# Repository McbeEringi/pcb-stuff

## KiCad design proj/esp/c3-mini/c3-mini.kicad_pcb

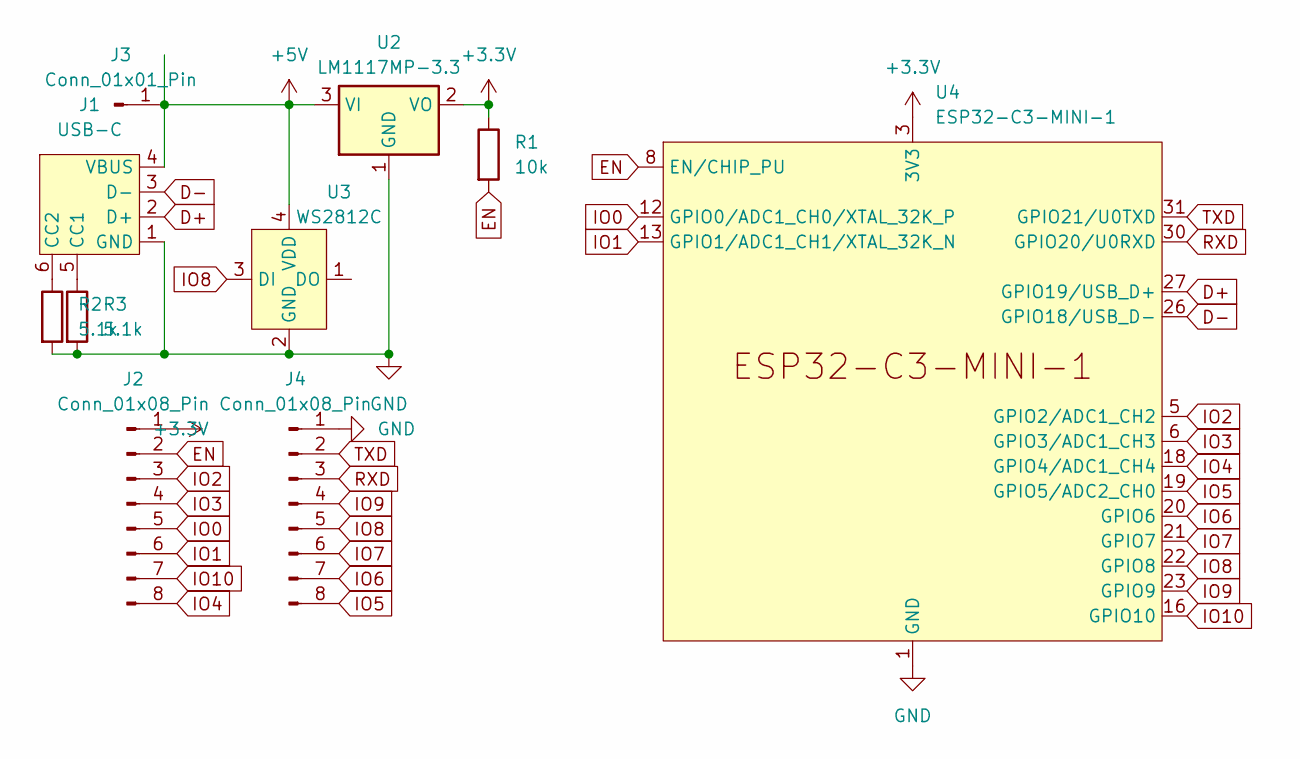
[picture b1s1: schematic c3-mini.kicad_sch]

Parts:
J1: USB-C
J2, J4: Conn_01x08_Pin; PinHeader_1x08_P2.54mm_Vertical
J3: Conn_01x01_Pin; PinHeader_1x01_P2.54mm_Vertical
R1: 10k; R_0603_1608Metric
R2, R3: 5.1k; R_0603_1608Metric
U2: LM1117MP-3.3; SOT-223-3_TabPin2
U3: WS2812C; WS2812C-2020
U4: ESP32-C3-MINI-1

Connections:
+3.3V: J2.1, R1.1, U2.2 (VO), U4.3 (3V3)
+5V: J1.4 (VBUS), J3.1, U2.3 (VI), U3.4 (VDD)
D+: J1.2 (D+), U4.27 (GPIO19/USB_D+)
D-: J1.3 (D-), U4.26 (GPIO18/USB_D-)
EN: J2.2, R1.2, U4.8 (EN/CHIP_PU)
GND: J1.1 (GND), J4.1, R2.2, R3.2, U2.1 (GND), U3.2 (GND), U4.1 (GND), U4.2 (GND), U4.11 (GND), U4.14 (GND), U4.36 (GND), U4.37 (GND), U4.38 (GND), U4.39 (GND), U4.40 (GND), U4.41 (GND), U4.42 (GND), U4.43 (GND), U4.44 (GND), U4.45 (GND), U4.46 (GND), U4.47 (GND), U4.48 (GND), U4.49 (GND), U4.50 (GND), U4.51 (GND), U4.52 (GND), U4.53 (GND)
IO0: J2.5, U4.12 (GPIO0/ADC1_CH0/XTAL_32K_P)
IO1: J2.6, U4.13 (GPIO1/ADC1_CH1/XTAL_32K_N)
IO2: J2.3, U4.5 (GPIO2/ADC1_CH2)
IO3: J2.4, U4.6 (GPIO3/ADC1_CH3)
IO4: J2.8, U4.18 (GPIO4/ADC1_CH4)
IO5: J4.8, U4.19 (GPIO5/ADC2_CH0)
IO6: J4.7, U4.20 (GPIO6)
IO7: J4.6, U4.21 (GPIO7)
IO8: J4.5, U3.3 (DI), U4.22 (GPIO8)
IO9: J4.4, U4.23 (GPIO9)
IO10: J2.7, U4.16 (GPIO10)
unnamed: J1.5 (CC1), R3.1
unnamed: J1.6 (CC2), R2.1
RXD: J4.3, U4.30 (GPIO20/U0RXD)
TXD: J4.2, U4.31 (GPIO21/U0TXD)

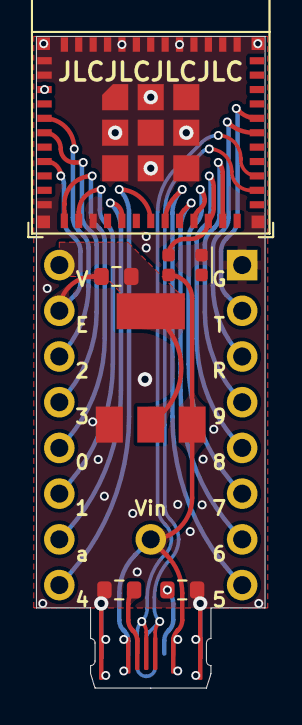
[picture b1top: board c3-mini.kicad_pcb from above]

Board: 2 copper layers, 12.7 x 36.2 mm, 10 parts (0 on the bottom side), 21 nets.

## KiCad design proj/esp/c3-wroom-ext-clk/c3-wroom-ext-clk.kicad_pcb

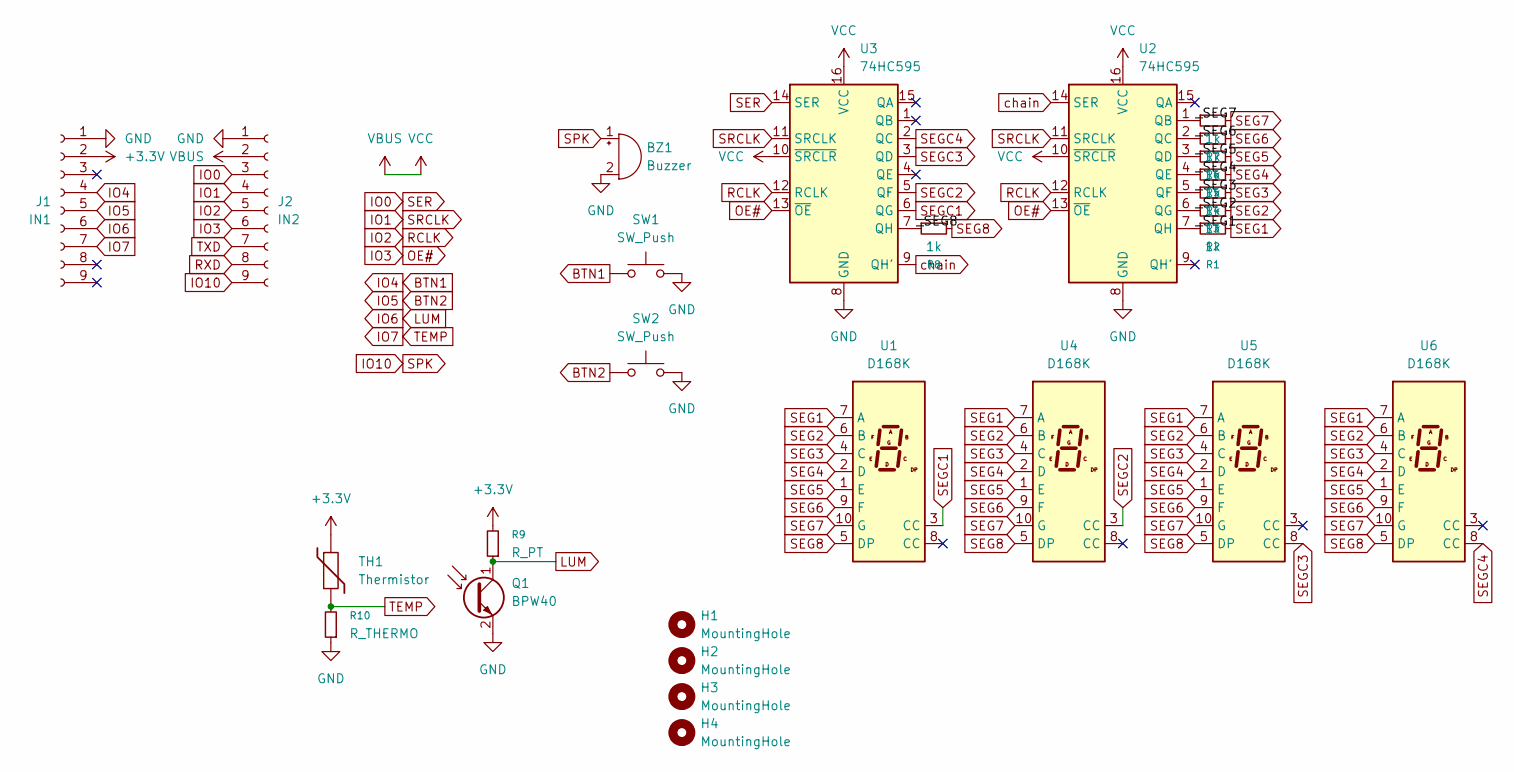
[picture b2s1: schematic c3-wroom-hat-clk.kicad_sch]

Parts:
BZ1: Buzzer; Buzzer_TDK_PS1240P02BT_D12.2mm_H6.5mm
H1, H2, H3, H4: MountingHole; MountingHole_3.2mm_M3
J1: IN1; PinSocket_1x09_P2.54mm_Vertical
J2: IN2; PinSocket_1x09_P2.54mm_Vertical
Q1: BPW40; LED_D5.0mm_Clear
R1, R2, R3, R4, R5, R6, R7, R8: 1k; R_0603_1608Metric
R9: R_PT; R_0603_1608Metric
R10: R_THERMO; R_0603_1608Metric
SW1, SW2: SW_Push; alps-skrg
TH1: Thermistor; R_0603_1608Metric
U1, U4, U5, U6: D168K; D1X8K
U2, U3: 74HC595; TSSOP-16_4.4x5mm_P0.65mm

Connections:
+3.3V: J1.2, R9.2, TH1.1
/_SEG1: R1.1, U2.7 (QH)
/_SEG2: R2.1, U2.6 (QG)
/_SEG3: R3.1, U2.5 (QF)
/_SEG4: R4.1, U2.4 (QE)
/_SEG5: R5.1, U2.3 (QD)
/_SEG6: R6.1, U2.2 (QC)
/_SEG7: R7.1, U2.1 (QB)
/_SEG8: R8.1, U3.7 (QH)
BTN1: J1.4, SW1.1
BTN2: J1.5, SW2.1
GND: BZ1.2 (-), J1.1, J2.1, Q1.2 (E), R10.1, SW1.2, SW2.2, U2.8 (GND), U3.8 (GND)
IO0: J2.3, U3.14 (SER)
IO1: J2.4, U2.11 (SRCLK), U3.11 (SRCLK)
IO2: J2.5, U2.12 (RCLK), U3.12 (RCLK)
IO3: J2.6, U2.13 (~OE), U3.13 (~OE)
IO6: J1.6, Q1.1 (C), R9.1
IO7: J1.7, R10.2, TH1.2
IO10: BZ1.1 (+), J2.9
RXD: J2.8
SEG1: R1.2, U1.7 (A), U4.7 (A), U5.7 (A), U6.7 (A)
SEG2: R2.2, U1.6 (B), U4.6 (B), U5.6 (B), U6.6 (B)
SEG3: R3.2, U1.4 (C), U4.4 (C), U5.4 (C), U6.4 (C)
SEG4: R4.2, U1.2 (D), U4.2 (D), U5.2 (D), U6.2 (D)
SEG5: R5.2, U1.1 (E), U4.1 (E), U5.1 (E), U6.1 (E)
SEG6: R6.2, U1.9 (F), U4.9 (F), U5.9 (F), U6.9 (F)
SEG7: R7.2, U1.10 (G), U4.10 (G), U5.10 (G), U6.10 (G)
SEG8: R8.2, U1.5 (DP), U4.5 (DP), U5.5 (DP), U6.5 (DP)
SEGC1: U1.3 (CC), U3.6 (QG)
SEGC2: U3.5 (QF), U4.3 (CC)
SEGC3: U3.3 (QD), U5.8 (CC)
SEGC4: U3.2 (QC), U6.8 (CC)
TXD: J2.7
VBUS: J2.2, U2.10 (~SRCLR), U2.16 (VCC), U3.10 (~SRCLR), U3.16 (VCC)
chain: U2.14 (SER), U3.9 (QH')

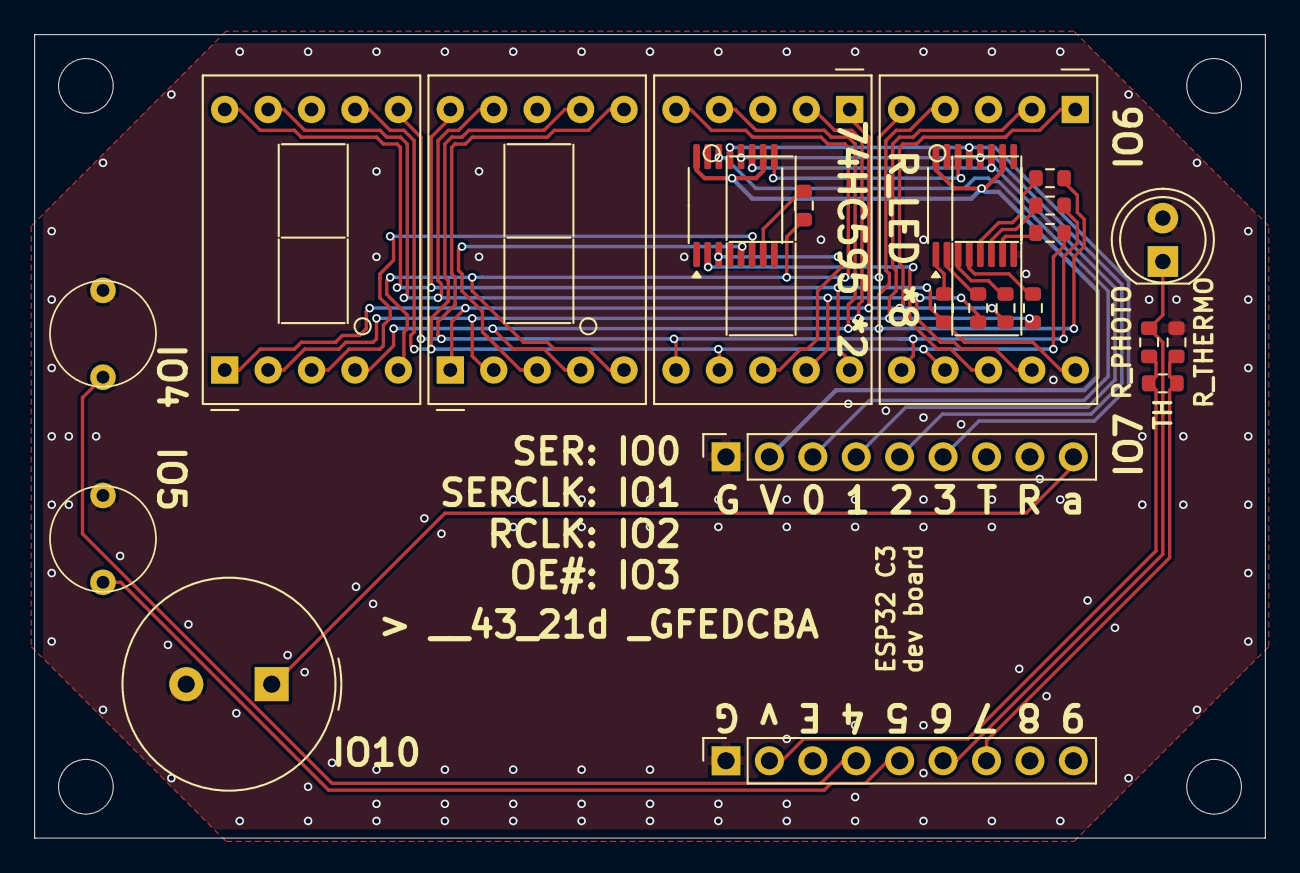
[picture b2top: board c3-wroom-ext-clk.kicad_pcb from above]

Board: 2 copper layers, 72.0 x 47.0 mm, 27 parts (0 on the bottom side), 33 nets.

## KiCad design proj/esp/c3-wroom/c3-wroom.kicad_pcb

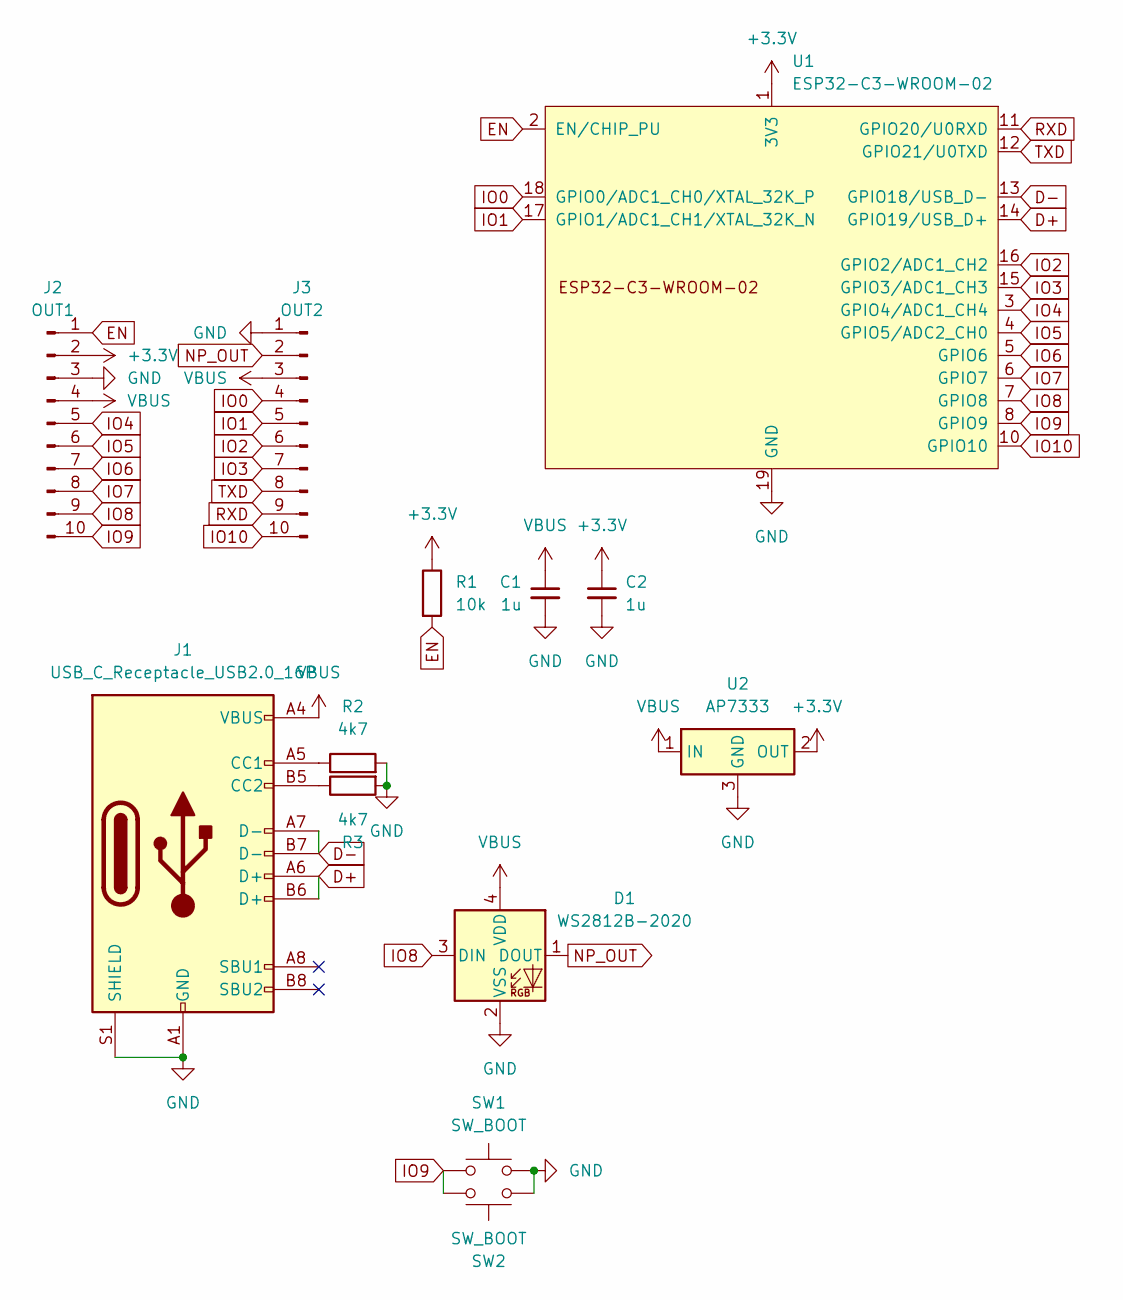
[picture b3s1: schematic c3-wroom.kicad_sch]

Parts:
C1, C2: 1u; C_0603_1608Metric
D1: WS2812B-2020; LED_WS2812B-2020_PLCC4_2.0x2.0mm
J1: USB_C_Receptacle_USB2.0_16P; USB_C_Receptacle_GCT_USB4105-xx-A_16P_TopMnt_Horizontal
J2: OUT1; PinHeader_1x10_P2.54mm_Vertical
J3: OUT2; PinHeader_1x10_P2.54mm_Vertical
R1: 10k; R_0603_1608Metric
R2, R3: 4k7; R_0603_1608Metric
SW1: SW_BOOT; alps-skrg
SW2: SW_BOOT; alps-skrp
U1: ESP32-C3-WROOM-02
U2: AP7333; SOT-23-3

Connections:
+3.3V: C2.1, J2.2, R1.1, U1.1 (3V3), U2.2 (OUT)
D+: J1.A6 (D+), J1.B6 (D+), U1.14 (GPIO19/USB_D+)
D-: J1.A7 (D-), J1.B7 (D-), U1.13 (GPIO18/USB_D-)
EN: J2.1, R1.2, U1.2 (EN/CHIP_PU)
GND: C1.2, C2.2, D1.2 (VSS), J1.A1 (GND), J1.A12 (GND), J1.B1 (GND), J1.B12 (GND), J1.S1 (SHIELD), J2.3, J3.1, R2.2, R3.2, SW1.2, SW2.2, U1.9 (GND), U1.19 (GND), U2.3 (GND)
IO0: J3.4, U1.18 (GPIO0/ADC1_CH0/XTAL_32K_P)
IO1: J3.5, U1.17 (GPIO1/ADC1_CH1/XTAL_32K_N)
IO2: J3.6, U1.16 (GPIO2/ADC1_CH2)
IO3: J3.7, U1.15 (GPIO3/ADC1_CH3)
IO4: J2.5, U1.3 (GPIO4/ADC1_CH4)
IO5: J2.6, U1.4 (GPIO5/ADC2_CH0)
IO6: J2.7, U1.5 (GPIO6)
IO7: J2.8, U1.6 (GPIO7)
IO8: D1.3 (DIN), J2.9, U1.7 (GPIO8)
IO9: J2.10, SW1.1, SW2.1, U1.8 (GPIO9)
IO10: J3.10, U1.10 (GPIO10)
NP_OUT: D1.1 (DOUT), J3.2
unnamed: J1.A5 (CC1), R2.1
unnamed: J1.B5 (CC2), R3.1
RXD: J3.9, U1.11 (GPIO20/U0RXD)
TXD: J3.8, U1.12 (GPIO21/U0TXD)
VBUS: C1.1, D1.4 (VDD), J1.A4 (VBUS), J1.A9 (VBUS), J1.B4 (VBUS), J1.B9 (VBUS), J2.4, J3.3, U2.1 (IN)

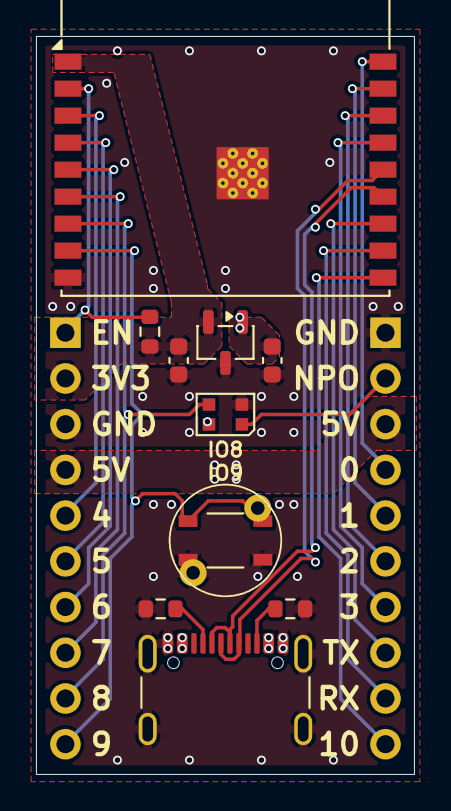
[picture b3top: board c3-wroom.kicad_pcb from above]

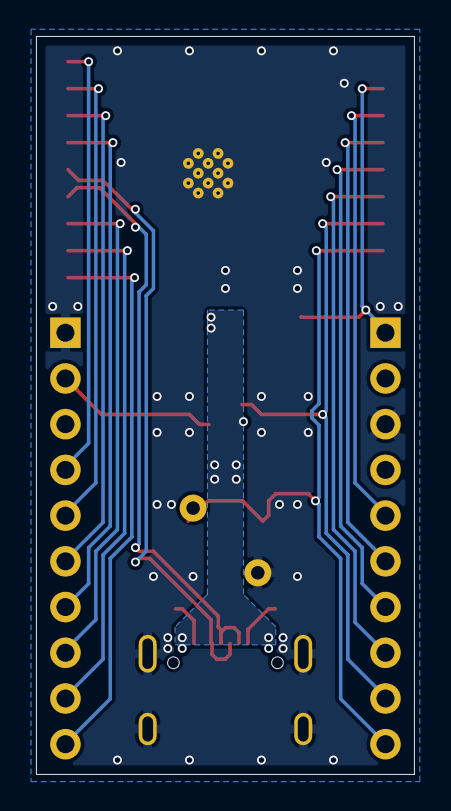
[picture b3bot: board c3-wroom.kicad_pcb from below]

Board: 2 copper layers, 21.0 x 41.0 mm, 13 parts (2 on the bottom side), 22 nets.

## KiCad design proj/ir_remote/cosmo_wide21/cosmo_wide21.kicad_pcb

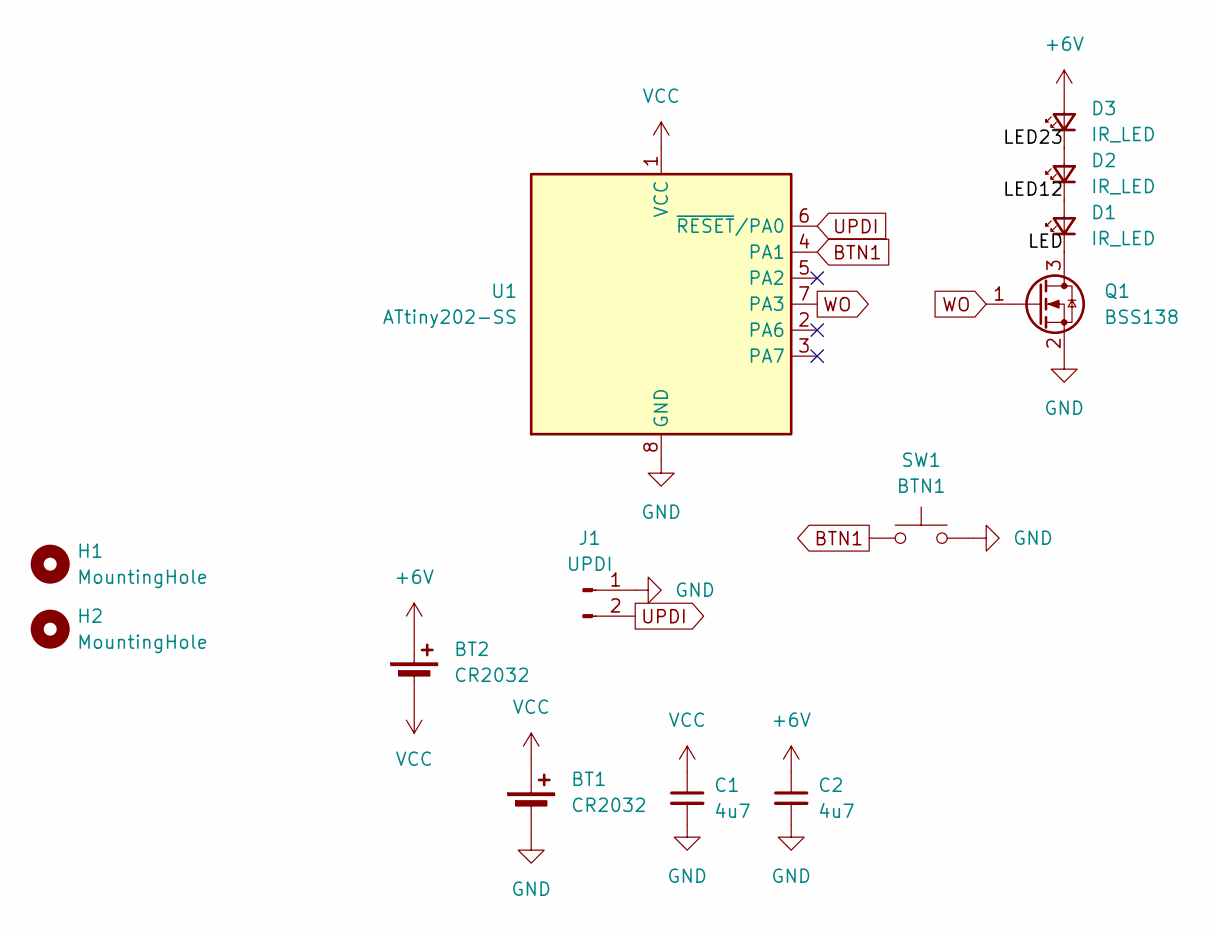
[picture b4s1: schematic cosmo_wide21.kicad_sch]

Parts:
BT1, BT2: CR2032; BatteryHolder_Multicomp_BC-2001_1x2032
C1, C2: 4u7; C_0603_1608Metric
D1, D2, D3: IR_LED; LED_D5.0mm_Horizontal_O1.27mm_Z3.0mm_Clear
H1, H2: MountingHole; MountingHole_3.2mm_M3
J1: UPDI; PinHeader_1x02_P2.54mm_Vertical
Q1: BSS138; SOT-23
SW1: BTN1; alps-skrg
U1: ATtiny202-SS; SOIC-8_3.9x4.9mm_P1.27mm

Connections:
+6V: BT2.1 (+), C2.1, D3.2 (A)
/LED: D1.1 (K), Q1.3 (D)
/LED12: D1.2 (A), D2.1 (K)
/LED23: D2.2 (A), D3.1 (K)
BTN1: SW1.1, U1.4 (PA1)
GND: BT1.2 (-), C1.2, C2.2, J1.1, Q1.2 (S), SW1.2, U1.8 (GND)
UPDI: J1.2, U1.6 (~RESET/PA0)
VCC: BT1.1 (+), BT2.2 (-), C1.1, U1.1 (VCC)
WO: Q1.1 (G), U1.7 (PA3)

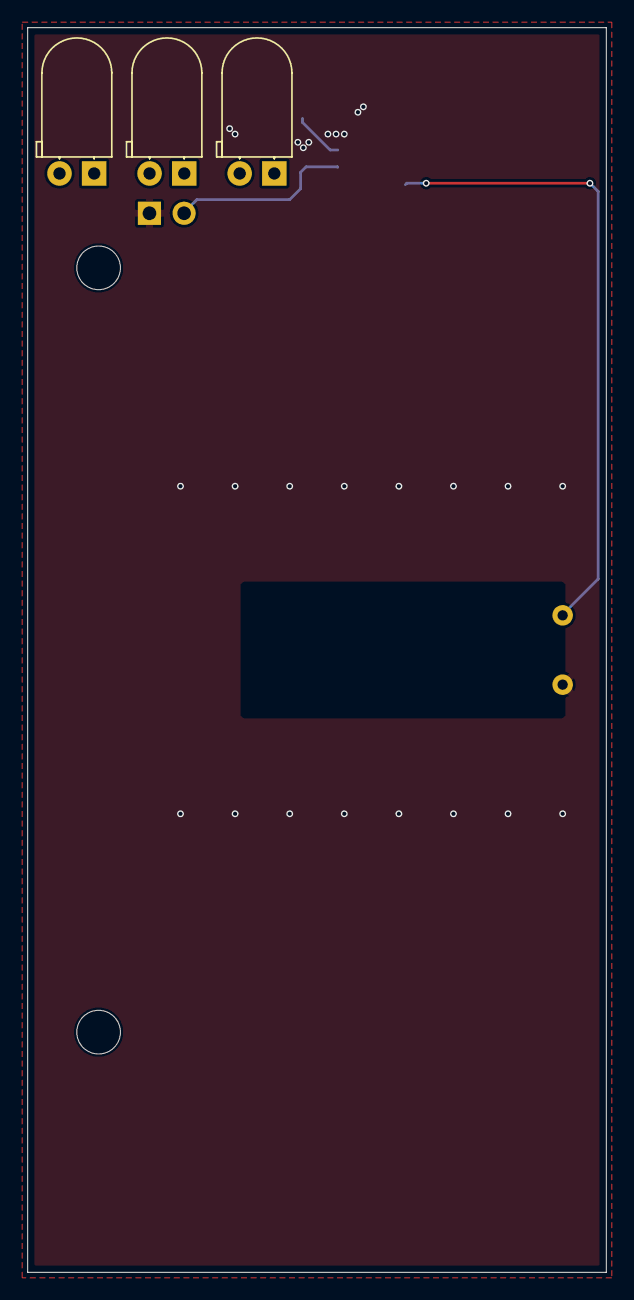
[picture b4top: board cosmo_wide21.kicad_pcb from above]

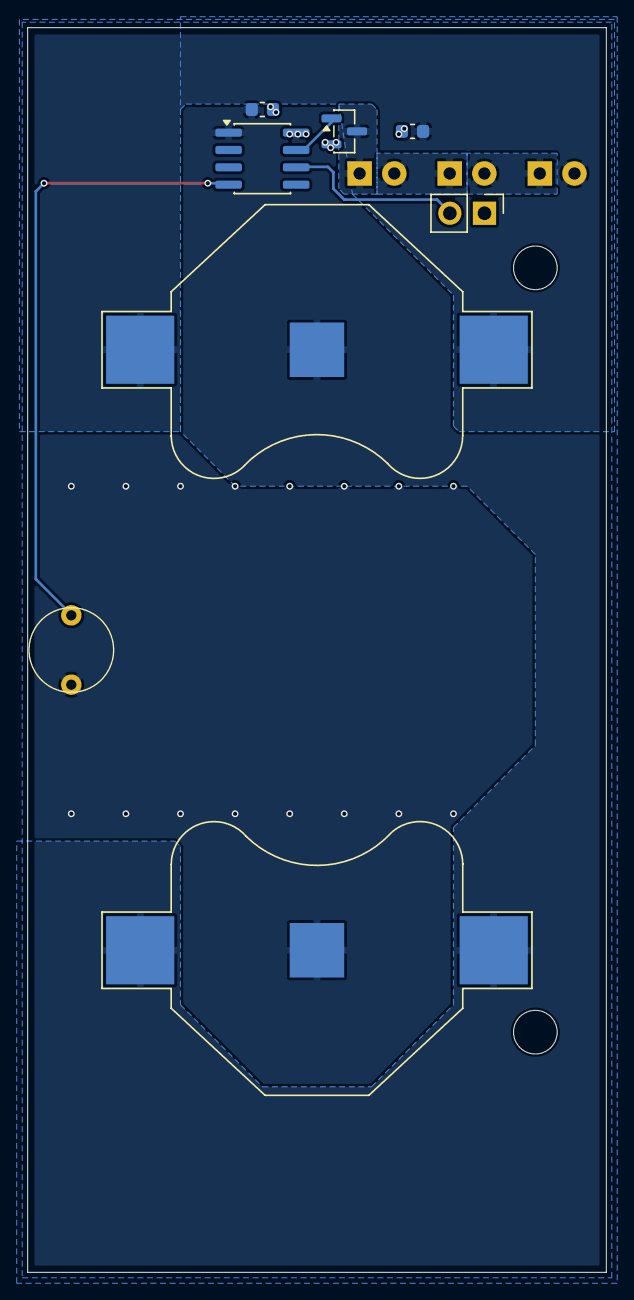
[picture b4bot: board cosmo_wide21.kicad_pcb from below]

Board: 2 copper layers, 42.4 x 91.2 mm, 13 parts (8 on the bottom side), 9 nets.

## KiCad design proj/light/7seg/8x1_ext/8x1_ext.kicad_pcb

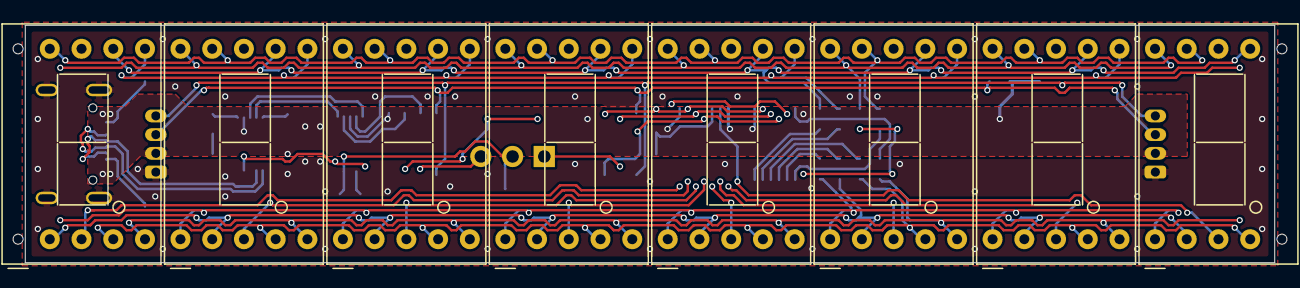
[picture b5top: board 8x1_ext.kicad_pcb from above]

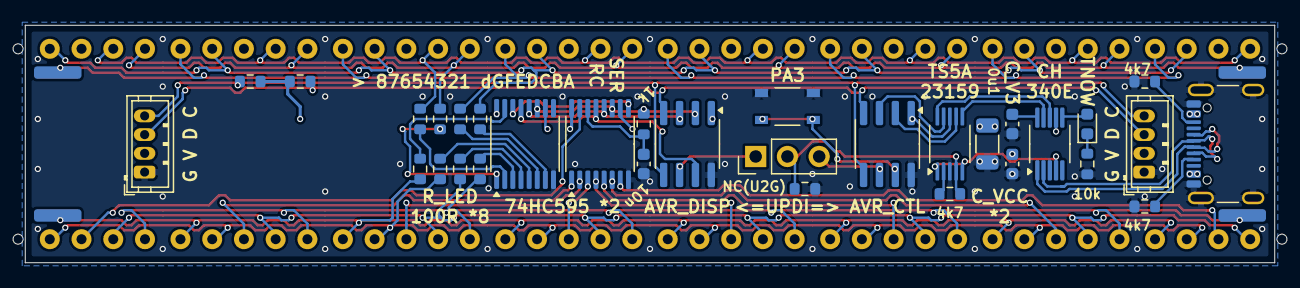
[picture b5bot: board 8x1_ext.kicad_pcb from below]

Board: 2 copper layers, 100.0 x 19.0 mm, 40 parts (32 on the bottom side), 50 nets.

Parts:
C1: 10n; C_0603_1608Metric
C2: 1u; C_0603_1608Metric
C3: 0u1; C_0603_1608Metric
C4: 100u; C_1206_3216Metric
D3: LED_TNOW; LED_0603_1608Metric
J2, J3: I2C; JST_ZH_B4B-ZR_1x04_P1.50mm_Vertical
J4: USB_C_Receptacle_USB2.0_16P; USB_C_Receptacle_GCT_USB4105-xx-A_16P_TopMnt_Horizontal
JP1: Jumper_3_Open; PinHeader_1x03_P2.54mm_Vertical
R1, R2, R3, R4, R5, R6, R7, R8: 100R; R_0603_1608Metric
R9: 1k; R_0603_1608Metric
R10, R11: 5k1; R_0603_1608Metric
R12: R_TNOW; R_0603_1608Metric
R13, R14, R15: 4k7; R_0603_1608Metric
R16: NC; R_0603_1608Metric
SW1: SW_Push; alps-skrp
U1, U2: 74HC595; TSSOP-16_4.4x5mm_P0.65mm
U3, U4, U5, U6, U7, U8, U9, U10: D168K; D1X8K
U11: AVR_DISP; SOIC-8_3.9x4.9mm_P1.27mm
U12: CH340E; MSOP-10_3x3mm_P0.5mm
U13: TS5A23159DGS; VSSOP-10_3x3mm_P0.5mm
U14: AVR_CTL; SOIC-8_3.9x4.9mm_P1.27mm

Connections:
/TNOW: D3.2 (A), U12.6 (TNOW)
/V3: C3.2, U12.10 (V3)
/_A: R1.1, U2.7 (QH)
/_B: R2.1, U2.6 (QG)
/_C: R3.1, U2.5 (QF)
/_D: R4.1, U2.4 (QE)
/_E: R5.1, U2.3 (QD)
/_F: R6.1, U2.2 (QC)
/_G: R7.1, U2.1 (QB)
/_H: R8.1, U2.15 (QA)
/chain: U1.9 (QH'), U2.14 (SER)
A: R1.2, U3.7 (A), U4.7 (A), U5.7 (A), U6.7 (A), U7.7 (A), U8.7 (A), U9.7 (A), U10.7 (A)
B: R2.2, U3.6 (B), U4.6 (B), U5.6 (B), U6.6 (B), U7.6 (B), U8.6 (B), U9.6 (B), U10.6 (B)
BTN: SW1.1, U14.7 (PA3)
C: R3.2, U3.4 (C), U4.4 (C), U5.4 (C), U6.4 (C), U7.4 (C), U8.4 (C), U9.4 (C), U10.4 (C)
C0: U1.7 (QH), U3.3 (CC)
C1: U1.6 (QG), U4.3 (CC)
C2: U1.5 (QF), U5.3 (CC)
C3: U1.4 (QE), U6.3 (CC)
C4: U1.3 (QD), U7.3 (CC)
C5: U1.2 (QC), U8.3 (CC)
C6: U1.1 (QB), U9.3 (CC)
C7: U1.15 (QA), U10.3 (CC)
D: R4.2, U3.2 (D), U4.2 (D), U5.2 (D), U6.2 (D), U7.2 (D), U8.2 (D), U9.2 (D), U10.2 (D)
D+: J4.A6 (D+), J4.B6 (D+), U12.1 (UD+)
D-: J4.A7 (D-), J4.B7 (D-), U12.2 (UD-)
E: R5.2, U3.1 (E), U4.1 (E), U5.1 (E), U6.1 (E), U7.1 (E), U8.1 (E), U9.1 (E), U10.1 (E)
F: R6.2, U3.9 (F), U4.9 (F), U5.9 (F), U6.9 (F), U7.9 (F), U8.9 (F), U9.9 (F), U10.9 (F)
G: R7.2, U3.10 (G), U4.10 (G), U5.10 (G), U6.10 (G), U7.10 (G), U8.10 (G), U9.10 (G), U10.10 (G)
GND: C1.2, C2.2, C3.1, C4.2, J2.1, J3.1, J4.A1 (GND), J4.A12 (GND), J4.B1 (GND), J4.B12 (GND), J4.S1 (SHIELD), R10.2, R11.2, R12.2, R16.2, SW1.2, U1.8 (GND), U2.8 (GND), U11.8 (GND), U12.3 (GND), U13.3 (GND), U14.8 (GND)
H: R8.2, U3.5 (DP), U4.5 (DP), U5.5 (DP), U6.5 (DP), U7.5 (DP), U8.5 (DP), U9.5 (DP), U10.5 (DP)
unnamed: D3.1 (K), R12.1
unnamed: J4.A5 (CC1), R10.1
unnamed: J4.B5 (CC2), R11.1
unnamed: R13.1, U13.2
OE#: U1.13 (~OE), U2.13 (~OE), U11.7 (PA3)
RCLK: U1.12 (RCLK), U2.12 (RCLK), U11.3 (PA7)
RTS#: U12.4 (~RTS), U13.1, U13.5
RXD_CTL: U13.9, U14.3 (PA7)
RXD_USB: U12.9 (RXD), U13.6
SCL: J2.4, J3.4, R15.2, U11.5 (PA2), U14.5 (PA2)
SDA: J2.3, J3.3, R14.2, U11.4 (PA1), U14.4 (PA1)
SER: C1.1, R9.1, U1.14 (SER)
SRCLK: R9.2, U1.11 (SRCLK), U2.11 (SRCLK), U11.2 (PA6)
TXD_CTL: U13.7, U14.2 (PA6)
TXD_USB: U12.8 (TXD), U13.10
UPDI: JP1.2 (C), R13.2, R16.1, U13.4
UPDI_CTL: JP1.3 (B), U14.6 (~RESET/PA0)
UPDI_DISP: JP1.1 (A), U11.6 (~RESET/PA0)
VCC: C2.1, C4.1, J2.2, J3.2, J4.A4 (VBUS), J4.A9 (VBUS), J4.B4 (VBUS), J4.B9 (VBUS), R14.1, R15.1, U1.10 (~SRCLR), U1.16 (VCC), U2.10 (~SRCLR), U2.16 (VCC), U11.1 (VCC), U12.7 (VCC), U13.8 (VCC), U14.1 (VCC)

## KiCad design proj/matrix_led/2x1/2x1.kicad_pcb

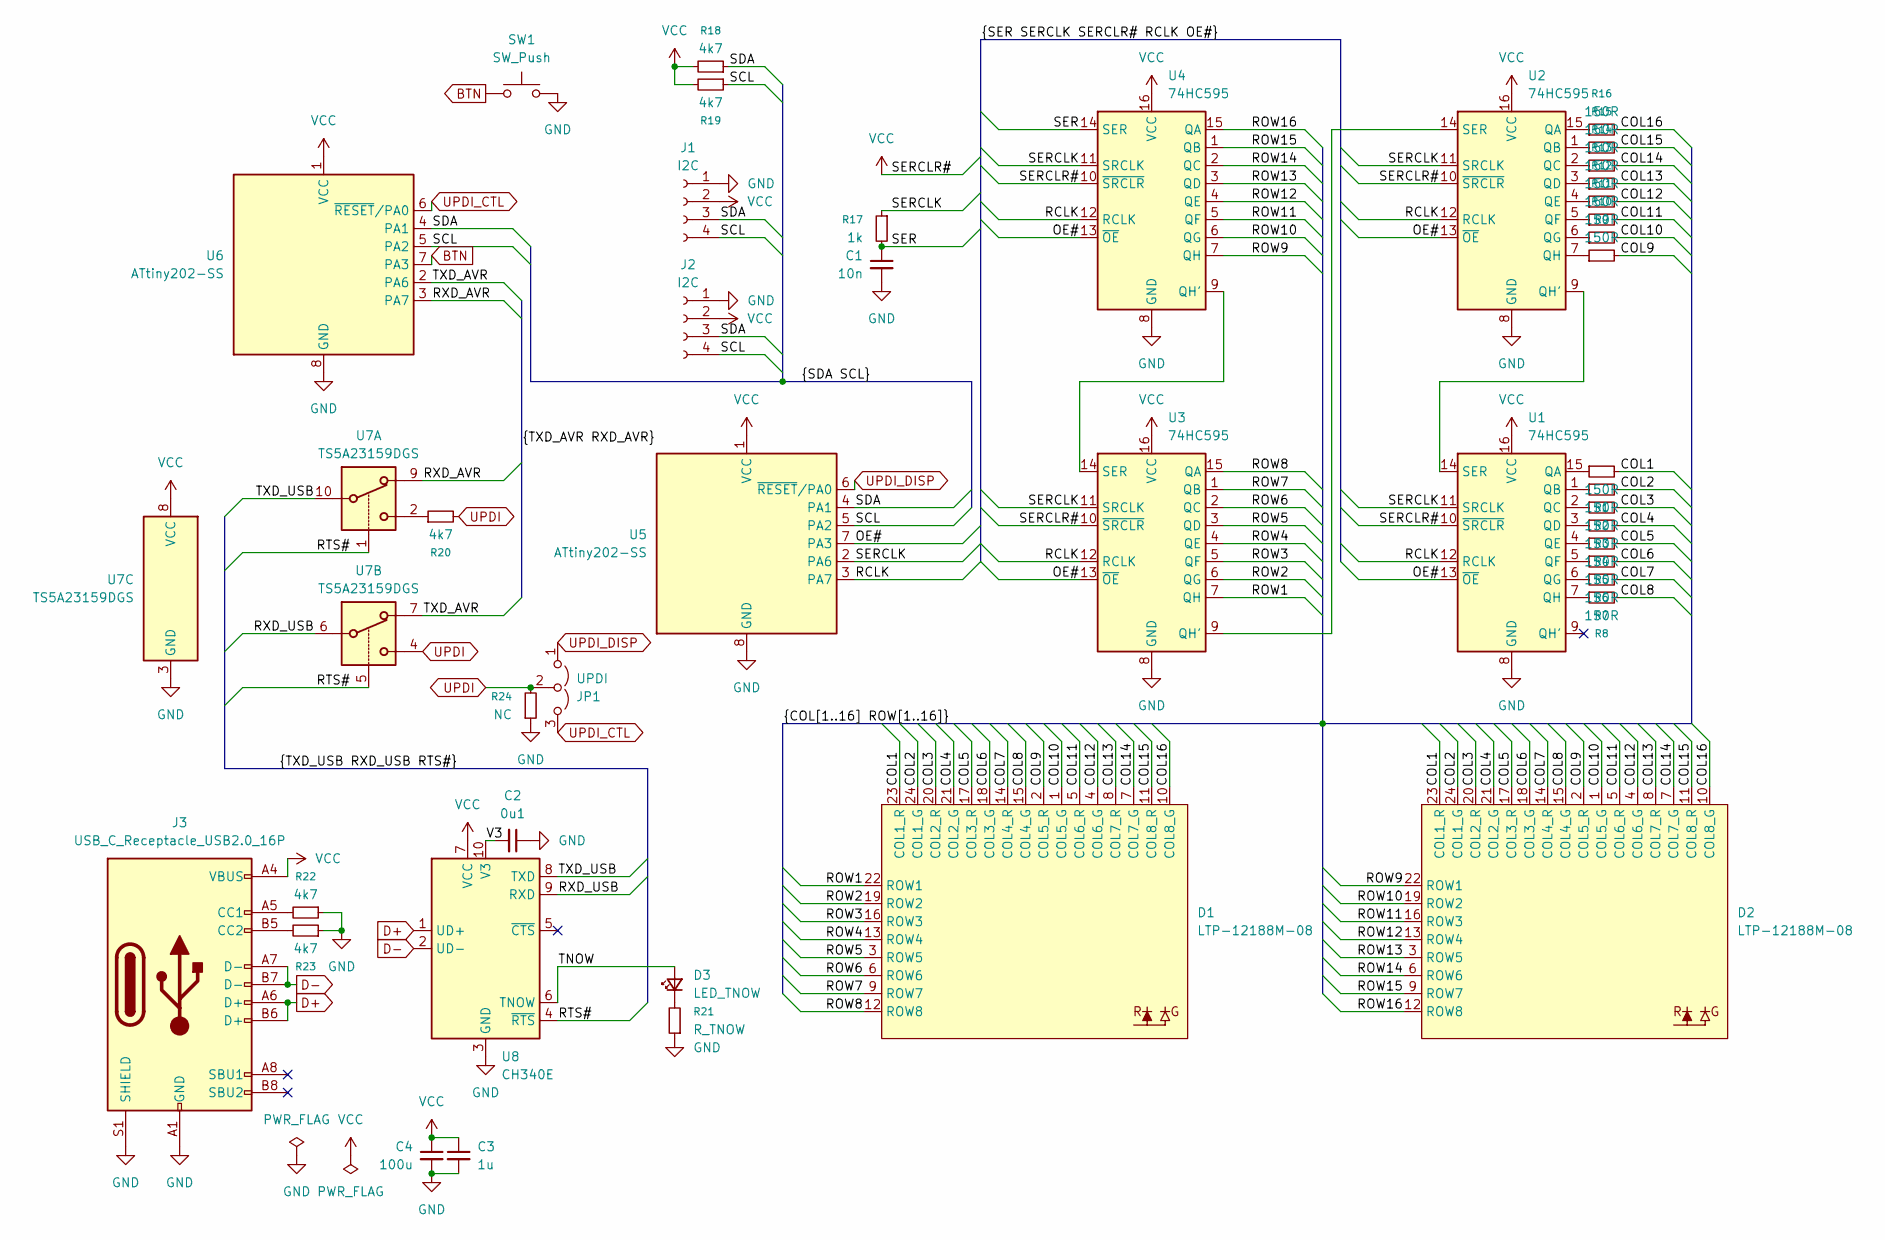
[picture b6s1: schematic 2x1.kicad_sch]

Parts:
C1: 10n; C_0603_1608Metric
C2: 0u1; C_0603_1608Metric
C3: 1u; C_0603_1608Metric
C4: 100u; C_1206_3216Metric
D1, D2: LTP-12188M-08
D3: LED_TNOW; LED_0603_1608Metric
J1, J2: I2C; JST_ZH_B4B-ZR_1x04_P1.50mm_Vertical
J3: USB_C_Receptacle_USB2.0_16P; USB_C_Receptacle_GCT_USB4105-xx-A_16P_TopMnt_Horizontal
JP1: UPDI; PinHeader_1x03_P1.27mm_Vertical
R1, R2, R3, R4, R5, R6, R7, R8, R9, R10, R11, R12, R13, R14, R15, R16: 150R; R_0603_1608Metric
R17: 1k; R_0603_1608Metric
R18, R19, R20, R22, R23: 4k7; R_0603_1608Metric
R21: R_TNOW; R_0603_1608Metric
R24: NC; R_0603_1608Metric
SW1: SW_Push; alps-skrp
U1, U2, U3, U4: 74HC595; TSSOP-16_4.4x5mm_P0.65mm
U5, U6: ATtiny202-SS; SOIC-8_3.9x4.9mm_P1.27mm
U7: TS5A23159DGS; VSSOP-10_3x3mm_P0.5mm
U8: CH340E; MSOP-10_3x3mm_P0.5mm

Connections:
/COL1: D1.23 (COL1_R), D2.23 (COL1_R), R1.2
/COL2: D1.24 (COL1_G), D2.24 (COL1_G), R2.2
/COL3: D1.20 (COL2_R), D2.20 (COL2_R), R3.2
/COL4: D1.21 (COL2_G), D2.21 (COL2_G), R4.2
/COL5: D1.17 (COL3_R), D2.17 (COL3_R), R5.2
/COL6: D1.18 (COL3_G), D2.18 (COL3_G), R6.2
/COL7: D1.14 (COL4_R), D2.14 (COL4_R), R7.2
/COL8: D1.15 (COL4_G), D2.15 (COL4_G), R8.2
/COL9: D1.2 (COL5_R), D2.2 (COL5_R), R9.2
/COL10: D1.1 (COL5_G), D2.1 (COL5_G), R10.2
/COL11: D1.5 (COL6_R), D2.5 (COL6_R), R11.2
/COL12: D1.4 (COL6_G), D2.4 (COL6_G), R12.2
/COL13: D1.8 (COL7_R), D2.8 (COL7_R), R13.2
/COL14: D1.7 (COL7_G), D2.7 (COL7_G), R14.2
/COL15: D1.11 (COL8_R), D2.11 (COL8_R), R15.2
/COL16: D1.10 (COL8_G), D2.10 (COL8_G), R16.2
/OE#: U1.13 (~OE), U2.13 (~OE), U3.13 (~OE), U4.13 (~OE), U5.7 (PA3)
/RCLK: U1.12 (RCLK), U2.12 (RCLK), U3.12 (RCLK), U4.12 (RCLK), U5.3 (PA7)
/ROW1: D1.22 (ROW1), U3.7 (QH)
/ROW2: D1.19 (ROW2), U3.6 (QG)
/ROW3: D1.16 (ROW3), U3.5 (QF)
/ROW4: D1.13 (ROW4), U3.4 (QE)
/ROW5: D1.3 (ROW5), U3.3 (QD)
/ROW6: D1.6 (ROW6), U3.2 (QC)
/ROW7: D1.9 (ROW7), U3.1 (QB)
/ROW8: D1.12 (ROW8), U3.15 (QA)
/ROW9: D2.22 (ROW1), U4.7 (QH)
/ROW10: D2.19 (ROW2), U4.6 (QG)
/ROW11: D2.16 (ROW3), U4.5 (QF)
/ROW12: D2.13 (ROW4), U4.4 (QE)
/ROW13: D2.3 (ROW5), U4.3 (QD)
/ROW14: D2.6 (ROW6), U4.2 (QC)
/ROW15: D2.9 (ROW7), U4.1 (QB)
/ROW16: D2.12 (ROW8), U4.15 (QA)
/RTS#: U7.1, U7.5, U8.4 (~RTS)
/RXD_AVR: U6.3 (PA7), U7.9
/RXD_USB: U7.6, U8.9 (RXD)
/SCL: J1.4, J2.4, R19.1, U5.5 (PA2), U6.5 (PA2)
/SDA: J1.3, J2.3, R18.1, U5.4 (PA1), U6.4 (PA1)
/SER: C1.1, R17.2, U4.14 (SER)
/SERCLK: R17.1, U1.11 (SRCLK), U2.11 (SRCLK), U3.11 (SRCLK), U4.11 (SRCLK), U5.2 (PA6)
/TNOW: D3.2 (A), U8.6 (TNOW)
/TXD_AVR: U6.2 (PA6), U7.7
/TXD_USB: U7.10, U8.8 (TXD)
/V3: C2.2, U8.10 (V3)
BTN: SW1.1, U6.7 (PA3)
D+: J3.A6 (D+), J3.B6 (D+), U8.1 (UD+)
D-: J3.A7 (D-), J3.B7 (D-), U8.2 (UD-)
GND: C1.2, C2.1, C3.2, C4.2, J1.1, J2.1, J3.A1 (GND), J3.A12 (GND), J3.B1 (GND), J3.B12 (GND), J3.S1 (SHIELD), R21.1, R22.1, R23.1, R24.1, SW1.2, U1.8 (GND), U2.8 (GND), U3.8 (GND), U4.8 (GND), U5.8 (GND), U6.8 (GND), U7.3 (GND), U8.3 (GND)
unnamed: D3.1 (K), R21.2
unnamed: J3.A5 (CC1), R22.2
unnamed: J3.B5 (CC2), R23.2
unnamed: R20.1, U7.2
unnamed: R1.1, U1.15 (QA)
unnamed: R2.1, U1.1 (QB)
unnamed: R3.1, U1.2 (QC)
unnamed: R4.1, U1.3 (QD)
unnamed: R5.1, U1.4 (QE)
unnamed: R6.1, U1.5 (QF)
unnamed: R7.1, U1.6 (QG)
unnamed: R8.1, U1.7 (QH)
unnamed: U1.14 (SER), U2.9 (QH')
unnamed: R16.1, U2.15 (QA)
unnamed: R15.1, U2.1 (QB)
unnamed: R14.1, U2.2 (QC)
unnamed: R13.1, U2.3 (QD)
unnamed: R12.1, U2.4 (QE)
unnamed: R11.1, U2.5 (QF)
unnamed: R10.1, U2.6 (QG)
unnamed: R9.1, U2.7 (QH)
unnamed: U2.14 (SER), U3.9 (QH')
unnamed: U3.14 (SER), U4.9 (QH')
UPDI: JP1.2 (C), R20.2, R24.2, U7.4
UPDI_CTL: JP1.3 (B), U6.6 (~RESET/PA0)
UPDI_DISP: JP1.1 (A), U5.6 (~RESET/PA0)
VCC: C3.1, C4.1, J1.2, J2.2, J3.A4 (VBUS), J3.A9 (VBUS), J3.B4 (VBUS), J3.B9 (VBUS), R18.2, R19.2, U1.10 (~SRCLR), U1.16 (VCC), U2.10 (~SRCLR), U2.16 (VCC), U3.10 (~SRCLR), U3.16 (VCC), U4.10 (~SRCLR), U4.16 (VCC), U5.1 (VCC), U6.1 (VCC), U7.8 (VCC), U8.7 (VCC)

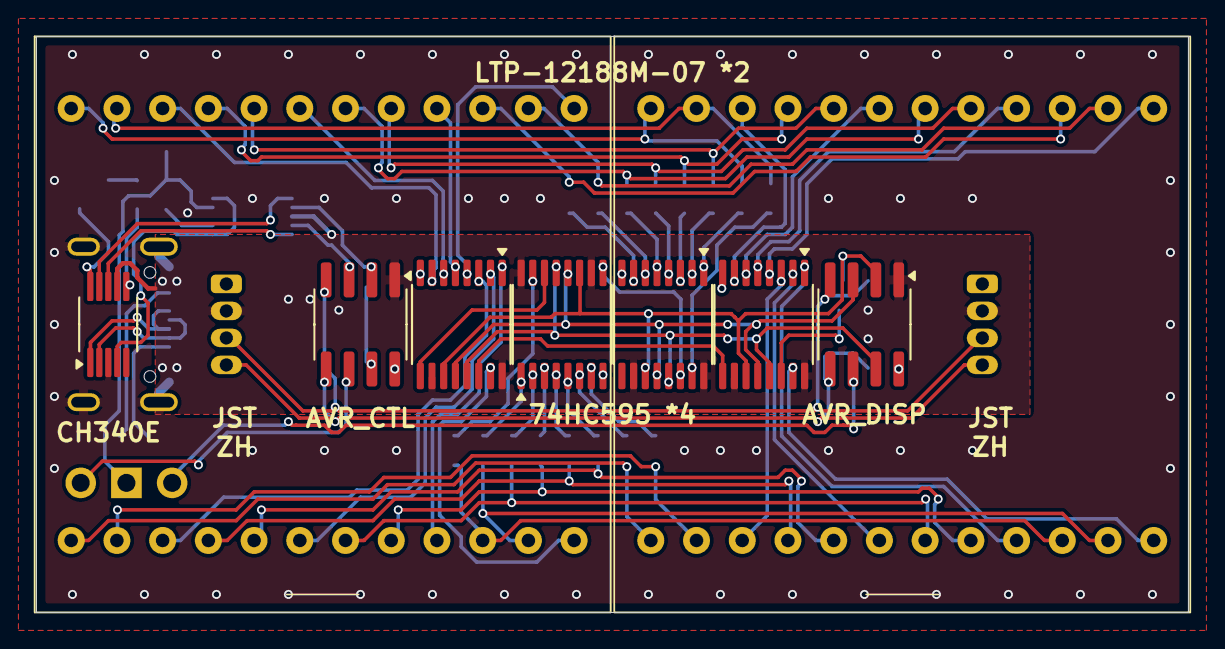
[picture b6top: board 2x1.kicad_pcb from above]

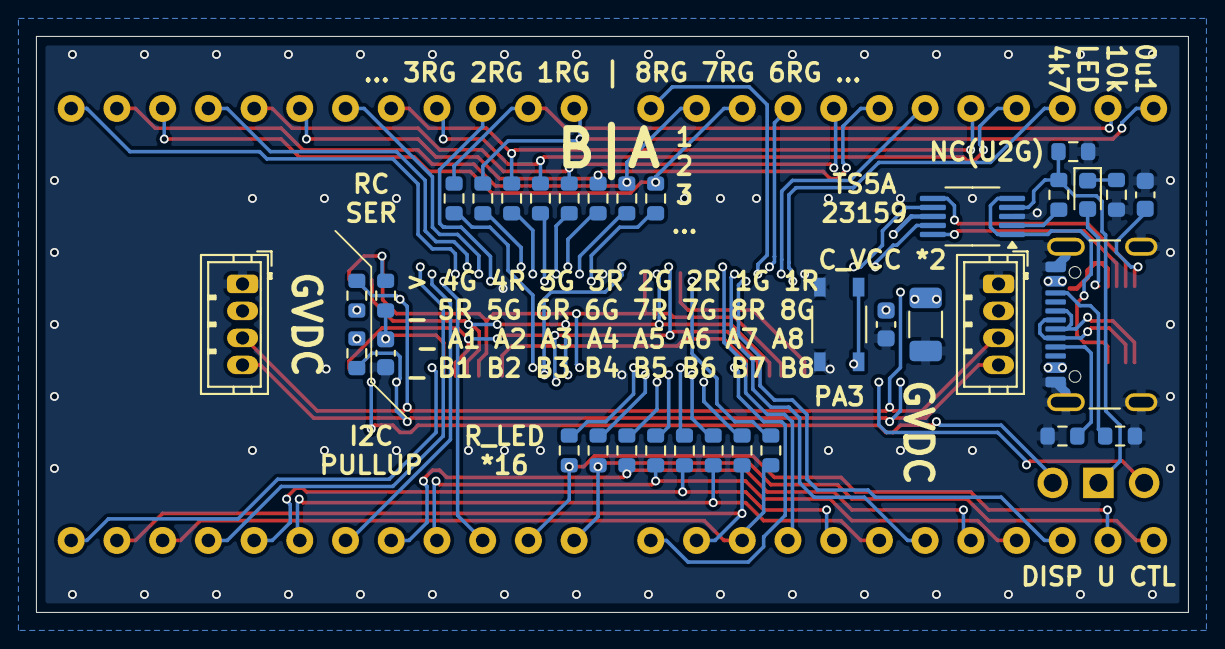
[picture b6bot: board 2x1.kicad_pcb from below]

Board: 2 copper layers, 64.0 x 32.0 mm, 44 parts (35 on the bottom side), 76 nets.
